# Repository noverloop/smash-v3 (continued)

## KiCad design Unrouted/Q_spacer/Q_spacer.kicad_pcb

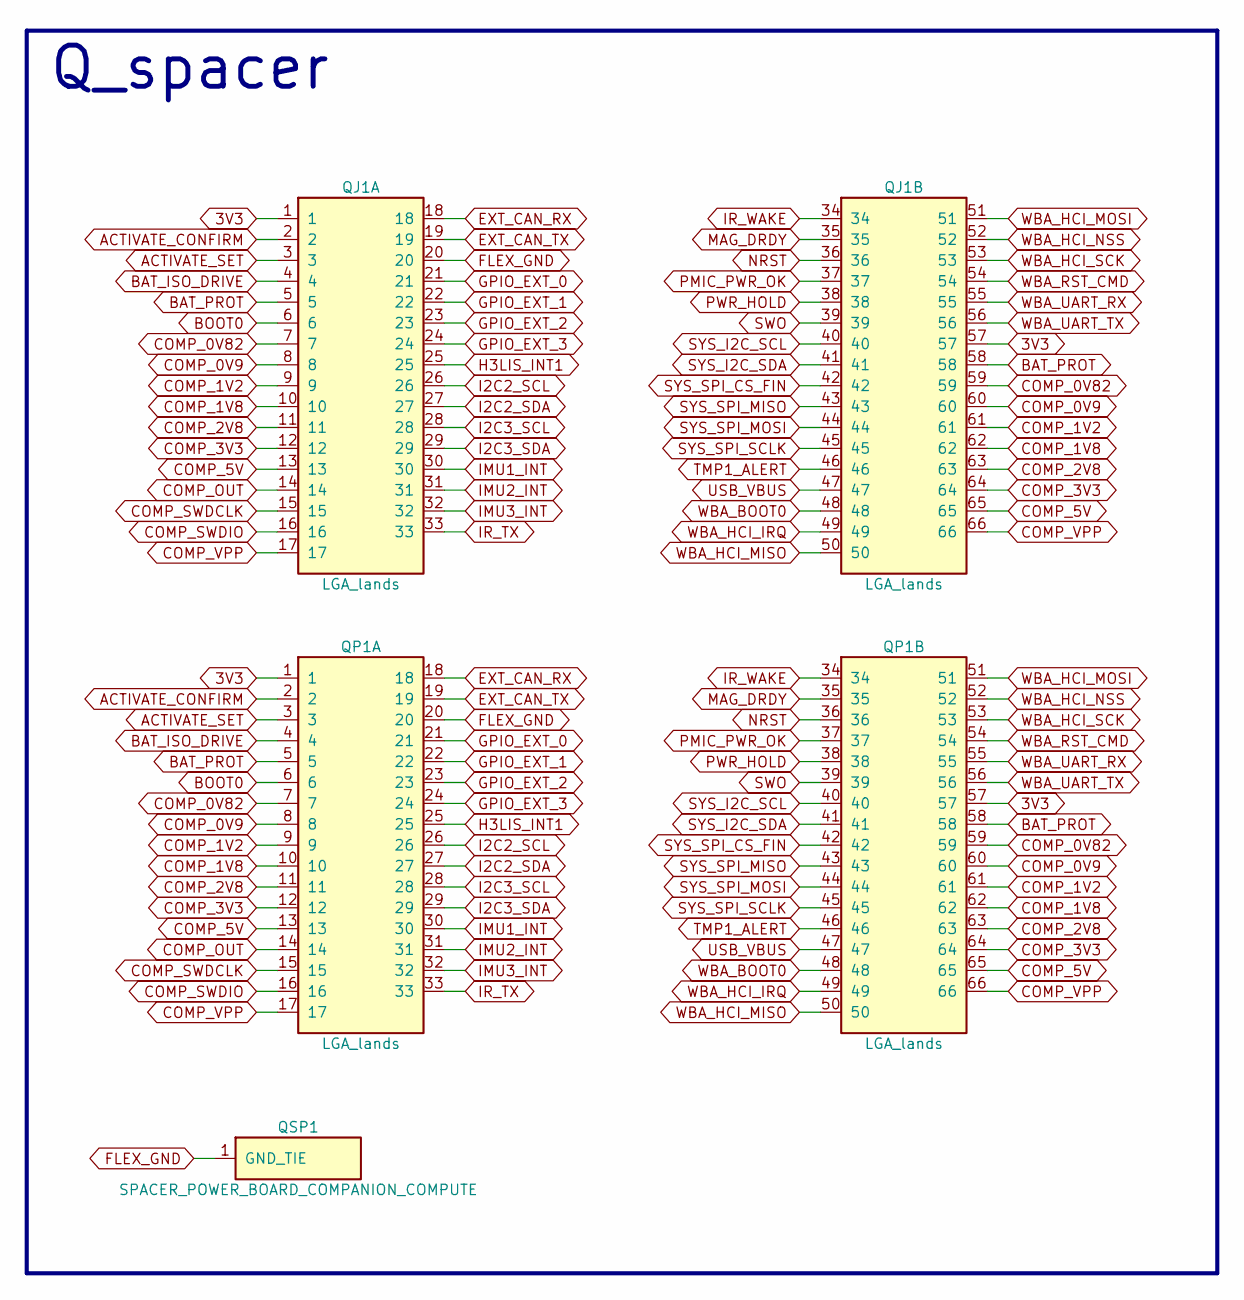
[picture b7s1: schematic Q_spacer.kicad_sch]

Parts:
QJ1: LGA_lands; J_spacer_power_board_companion_compute_top; MPN LGA_lands
QP1: LGA_lands; P_spacer_power_board_companion_compute_bot; MPN LGA_lands
QSP1: SPACER_POWER_BOARD_COMPANION_COMPUTE; Spacer_Mechanical_34mm

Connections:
3V3: QJ1.1, QJ1.57, QP1.1, QP1.57
ACTIVATE_CONFIRM: QJ1.2, QP1.2
ACTIVATE_SET: QJ1.3, QP1.3
BAT_ISO_DRIVE: QJ1.4, QP1.4
BAT_PROT: QJ1.5, QJ1.58, QP1.5, QP1.58
BOOT0: QJ1.6, QP1.6
COMP_0V9: QJ1.8, QJ1.60, QP1.8, QP1.60
COMP_0V82: QJ1.7, QJ1.59, QP1.7, QP1.59
COMP_1V2: QJ1.9, QJ1.61, QP1.9, QP1.61
COMP_1V8: QJ1.10, QJ1.62, QP1.10, QP1.62
COMP_2V8: QJ1.11, QJ1.63, QP1.11, QP1.63
COMP_3V3: QJ1.12, QJ1.64, QP1.12, QP1.64
COMP_5V: QJ1.13, QJ1.65, QP1.13, QP1.65
COMP_OUT: QJ1.14, QP1.14
COMP_SWDCLK: QJ1.15, QP1.15
COMP_SWDIO: QJ1.16, QP1.16
COMP_VPP: QJ1.17, QJ1.66, QP1.17, QP1.66
EXT_CAN_RX: QJ1.18, QP1.18
EXT_CAN_TX: QJ1.19, QP1.19
FLEX_GND: QJ1.20, QP1.20, QSP1.1
GPIO_EXT_0: QJ1.21, QP1.21
GPIO_EXT_1: QJ1.22, QP1.22
GPIO_EXT_2: QJ1.23, QP1.23
GPIO_EXT_3: QJ1.24, QP1.24
H3LIS_INT1: QJ1.25, QP1.25
I2C2_SCL: QJ1.26, QP1.26
I2C2_SDA: QJ1.27, QP1.27
I2C3_SCL: QJ1.28, QP1.28
I2C3_SDA: QJ1.29, QP1.29
IMU1_INT: QJ1.30, QP1.30
IMU2_INT: QJ1.31, QP1.31
IMU3_INT: QJ1.32, QP1.32
IR_TX: QJ1.33, QP1.33
IR_WAKE: QJ1.34, QP1.34
MAG_DRDY: QJ1.35, QP1.35
NRST: QJ1.36, QP1.36
PMIC_PWR_OK: QJ1.37, QP1.37
PWR_HOLD: QJ1.38, QP1.38
SWO: QJ1.39, QP1.39
SYS_I2C_SCL: QJ1.40, QP1.40
SYS_I2C_SDA: QJ1.41, QP1.41
SYS_SPI_CS_FIN: QJ1.42, QP1.42
SYS_SPI_MISO: QJ1.43, QP1.43
SYS_SPI_MOSI: QJ1.44, QP1.44
SYS_SPI_SCLK: QJ1.45, QP1.45
TMP1_ALERT: QJ1.46, QP1.46
USB_VBUS: QJ1.47, QP1.47
WBA_BOOT0: QJ1.48, QP1.48
WBA_HCI_IRQ: QJ1.49, QP1.49
WBA_HCI_MISO: QJ1.50, QP1.50
WBA_HCI_MOSI: QJ1.51, QP1.51
WBA_HCI_NSS: QJ1.52, QP1.52
WBA_HCI_SCK: QJ1.53, QP1.53
WBA_RST_CMD: QJ1.54, QP1.54
WBA_UART_RX: QJ1.55, QP1.55
WBA_UART_TX: QJ1.56, QP1.56

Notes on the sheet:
Q_spacer

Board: 2 copper layers, 5 parts (1 on the bottom side), 56 nets, no tracks yet.

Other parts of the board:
QMH1, QMH2: smash_mech_potting

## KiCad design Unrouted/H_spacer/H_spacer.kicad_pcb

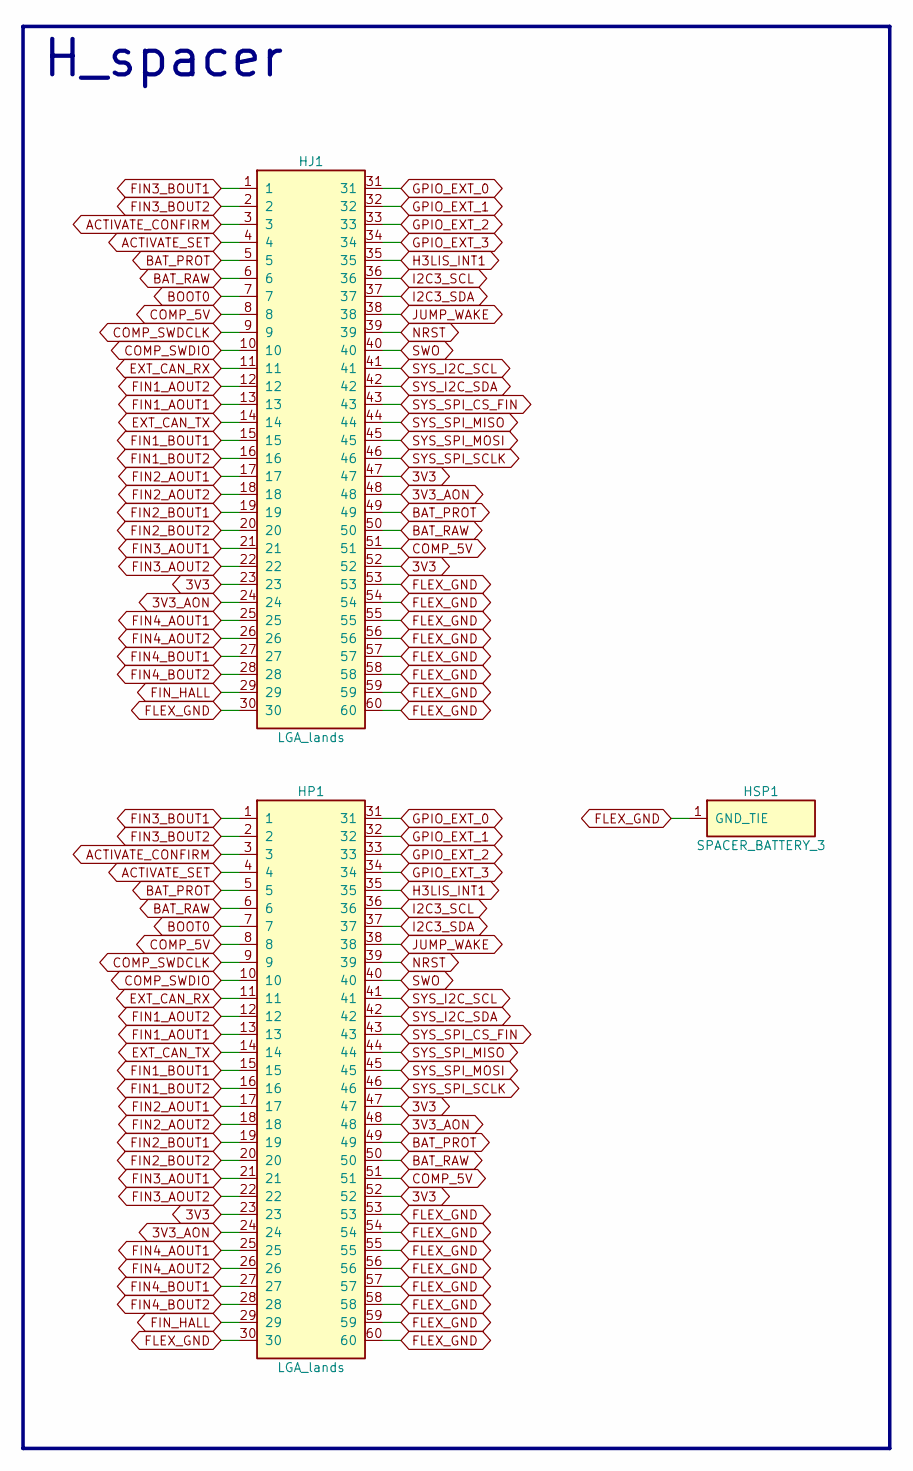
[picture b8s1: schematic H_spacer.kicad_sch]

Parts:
HJ1: LGA_lands; J_spacer_battery_3_top; MPN LGA_lands
HP1: LGA_lands; P_spacer_battery_3_bot; MPN LGA_lands
HSP1: SPACER_BATTERY_3; Spacer_Mechanical_34mm

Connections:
3V3: HJ1.23, HJ1.47, HJ1.52, HP1.23, HP1.47, HP1.52
3V3_AON: HJ1.24, HJ1.48, HP1.24, HP1.48
ACTIVATE_CONFIRM: HJ1.3, HP1.3
ACTIVATE_SET: HJ1.4, HP1.4
BAT_PROT: HJ1.5, HJ1.49, HP1.5, HP1.49
BAT_RAW: HJ1.6, HJ1.50, HP1.6, HP1.50
BOOT0: HJ1.7, HP1.7
COMP_5V: HJ1.8, HJ1.51, HP1.8, HP1.51
COMP_SWDCLK: HJ1.9, HP1.9
COMP_SWDIO: HJ1.10, HP1.10
EXT_CAN_RX: HJ1.11, HP1.11
EXT_CAN_TX: HJ1.14, HP1.14
FIN1_AOUT1: HJ1.13, HP1.13
FIN1_AOUT2: HJ1.12, HP1.12
FIN1_BOUT1: HJ1.15, HP1.15
FIN1_BOUT2: HJ1.16, HP1.16
FIN2_AOUT1: HJ1.17, HP1.17
FIN2_AOUT2: HJ1.18, HP1.18
FIN2_BOUT1: HJ1.19, HP1.19
FIN2_BOUT2: HJ1.20, HP1.20
FIN3_AOUT1: HJ1.21, HP1.21
FIN3_AOUT2: HJ1.22, HP1.22
FIN3_BOUT1: HJ1.1, HP1.1
FIN3_BOUT2: HJ1.2, HP1.2
FIN4_AOUT1: HJ1.25, HP1.25
FIN4_AOUT2: HJ1.26, HP1.26
FIN4_BOUT1: HJ1.27, HP1.27
FIN4_BOUT2: HJ1.28, HP1.28
FIN_HALL: HJ1.29, HP1.29
FLEX_GND: HJ1.30, HJ1.53, HJ1.54, HJ1.55, HJ1.56, HJ1.57, HJ1.58, HJ1.59, HJ1.60, HP1.30, HP1.53, HP1.54, HP1.55, HP1.56, HP1.57, HP1.58, HP1.59, HP1.60, HSP1.1
GPIO_EXT_0: HJ1.31, HP1.31
GPIO_EXT_1: HJ1.32, HP1.32
GPIO_EXT_2: HJ1.33, HP1.33
GPIO_EXT_3: HJ1.34, HP1.34
H3LIS_INT1: HJ1.35, HP1.35
I2C3_SCL: HJ1.36, HP1.36
I2C3_SDA: HJ1.37, HP1.37
JUMP_WAKE: HJ1.38, HP1.38
NRST: HJ1.39, HP1.39
SWO: HJ1.40, HP1.40
SYS_I2C_SCL: HJ1.41, HP1.41
SYS_I2C_SDA: HJ1.42, HP1.42
SYS_SPI_CS_FIN: HJ1.43, HP1.43
SYS_SPI_MISO: HJ1.44, HP1.44
SYS_SPI_MOSI: HJ1.45, HP1.45
SYS_SPI_SCLK: HJ1.46, HP1.46

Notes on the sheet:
H_spacer

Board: 2 copper layers, 4 parts (1 on the bottom side), 46 nets, no tracks yet.

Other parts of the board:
HMH1: smash_mech_potting

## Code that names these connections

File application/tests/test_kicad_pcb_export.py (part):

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    # shock/launch disk gets 2 aft solder pads (P_PIEZO, below the battery) + a
    # charge-bleed R; the LMV331 comparator + its threshold network + 3V3
    # decoupling (C_COMP_PZ) relocate there from flight_board (so the high-Z
    # piezo node is local; only COMP_OUT crosses to the M33 PD5 EXTI). The
    # hardware confirm AND-gate (U_AND_CONFIRM) is retired — ACTIVATE_SET /
    # ACTIVATE_CONFIRM are firmware GPIOs. Net +1 (−U_AND_CONFIRM, +P_PIEZO,
    # +R_PIEZO_BLEED; comparator + caps relocated, not added).
    # → 402: nose contact switch deleted (−J_NOSE_CONTACT_A/B pads + their
    # R_NOSE_CONTACT_PU pull-up) — the aft piezo disk already senses impact via
    # the deceleration, so the tip switch was redundant. Nose down to 5 pads.
    # → 393: radar power switch deleted (−Q_RADAR_SW P-FET, −Q_RADAR_LVL BSS138
    # level-shifter, −R_RADAR_GATE_PU, −C_RADAR_BAT1/2) — the AWR buck + LDO now
    # tap always-on BAT_PROT and self-gate via their EN pins tied to RADAR_EN;
    # the RADAR_EN pull-down re-homes flight→radar. −5 parts + −4 LGA lands (the
    # adaptive densify recomputes as BAT_PROT/RADAR_EN move onto compute↔radar
    # while RADAR_BAT drops off 3 gaps) = −9.
    # → 396: nose status LED reverted from the 1-part SK6812MINI to a green/red
    # 0603 pair (D_NOSE_G + D_NOSE_R) + 2 current-limit resistors — the SK6812's
    # 5 V VDD needed a 3.5 V WS2812 DIN, out of spec for the 3.3 V GPIO. Both
    # LEDs V_F ~2 V, common-anode on BAT_PROT, M33 sinks each cathode (PG7/PG8).
    # Net +3 parts (merge of feat/nose-status-led-rg onto the radar-gating base).
    # → 395: launch comparator swapped LMV331 → TLV3691 (nanopower, ~0.15 µA) so it
    # stops being an ~80 µA shelf load on the always-on 3V3. Its push-pull output
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    # → 452: rule-sweep F1 fix — MP25→WBA reset made open-drain
    #   (Q_WBA_RST BSS138 + R_WBARST_PD 100k on wakeup, bottom face:
    #   top threw WBA_UART_* off the wakeup↔power lands). PB3 is a TT
    #   pin clamped to VDDIO4/COMP_3V3; tied directly onto the
    #   3V3_AON-pulled WBA_NRST it back-fed ~280 µA through the dead
    #   MP25 all standby. Gate has no clamp path; PB3 HIGH = reset.
    #   (+2: Q_WBA_RST, R_WBARST_PD.)
    # → 501: aft activation array — 12-sector capacitive-discharge
    #   (all on aft_end_board). TPS61175 #2 charges a
    #   25SVPF330M (Panasonic polymer, beside the cell) to ~19.7 V
    #   ACTIVATE_HV; CD74HC4514 4-to-16 decoder (BAT_PROT-powered, GPIO_EXT
    #   address) → 12× DMN6075 low-side select NFETs; DMP6110 high-side
    #   ACTIVATION (ACTIVATE_SET, resistor-divider gate clamp) isolates the
    #   charged cap until unlock; HV monitor → ACTIVATE_CONFIRM ADC;
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    #   D_IR_TX VSMB1940X01 940 nm emitter + tile-local keyer on
    #   radar_module (+Q_IR_TX BSS138, +R_IR_TX_A/B split current pair,
    #   +R_IR_TX_G/+R_IR_TX_PD gate parts, +C_IR_TX burst reservoir);
    #   gate net IR_TX → WBA PA6. ST25DV VCC session-gated from WBA PA7
    #   (net ST25DV_VCC — rail move only, ±0 parts; its CNFC_VCC/VCC2
    #   decoupling followed the net). −5 +7 = net +2.
    # → 511: back-fill for the wake rework pair (2026-07-30 — BOTH wake
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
